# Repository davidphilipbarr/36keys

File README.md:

# So what we got here then? 

Behold. Here are some really basic PCBs that only support kailh choc low profile switches.

Currently they mostly have 36 keys (or less) which I consider to be as small as a keyboard can be without resorting to chording or other shenanigans.

Proceed with caution, and a little apprehension.

## About

The splits are heavily influenced by the following keyboards, and actually based on foostan's corne-light pin layout and pcb. 

* 5plit
* Gergoplex
* crkbd
* Kyria
* Jian/Jorne/Jorian
* Ferris
* Squiggle

## Caseless

These are all supposed to be used caseless and have no holes for cases or anything fancy.

## Firmware

Most 36 key split pcbs can use the crkbd firmware, but not the ones with no diodes, these all use the cradio firmware, maybe such things can be found [here](qmk). 
There is also a stripped back 36 key firmware called cranorm, which can be used instead of the crkbd firmware.

## FAQs

Aren't all the splits basically the same board with the keys shuffled around? Yes.

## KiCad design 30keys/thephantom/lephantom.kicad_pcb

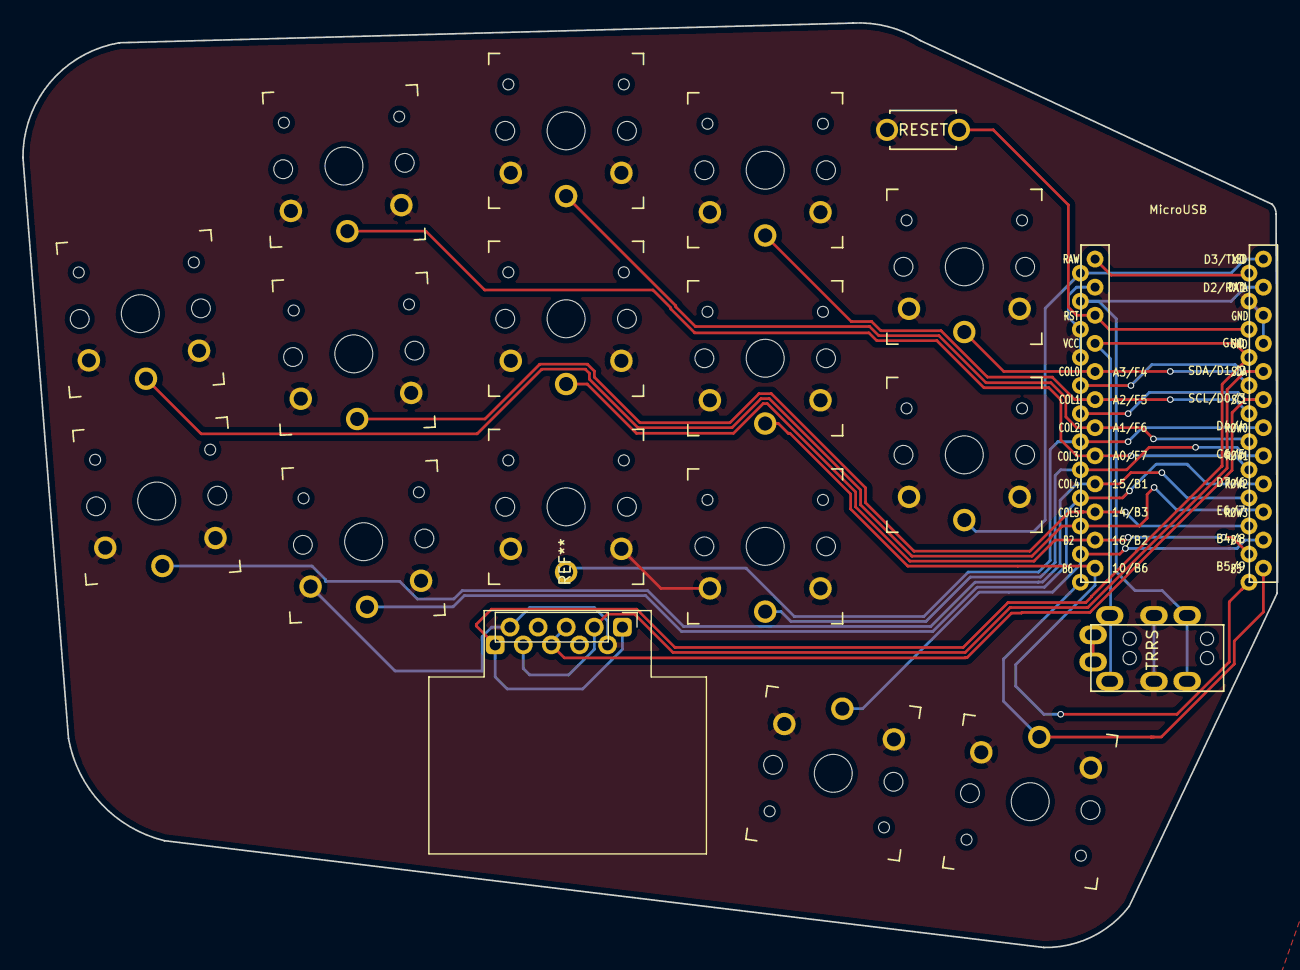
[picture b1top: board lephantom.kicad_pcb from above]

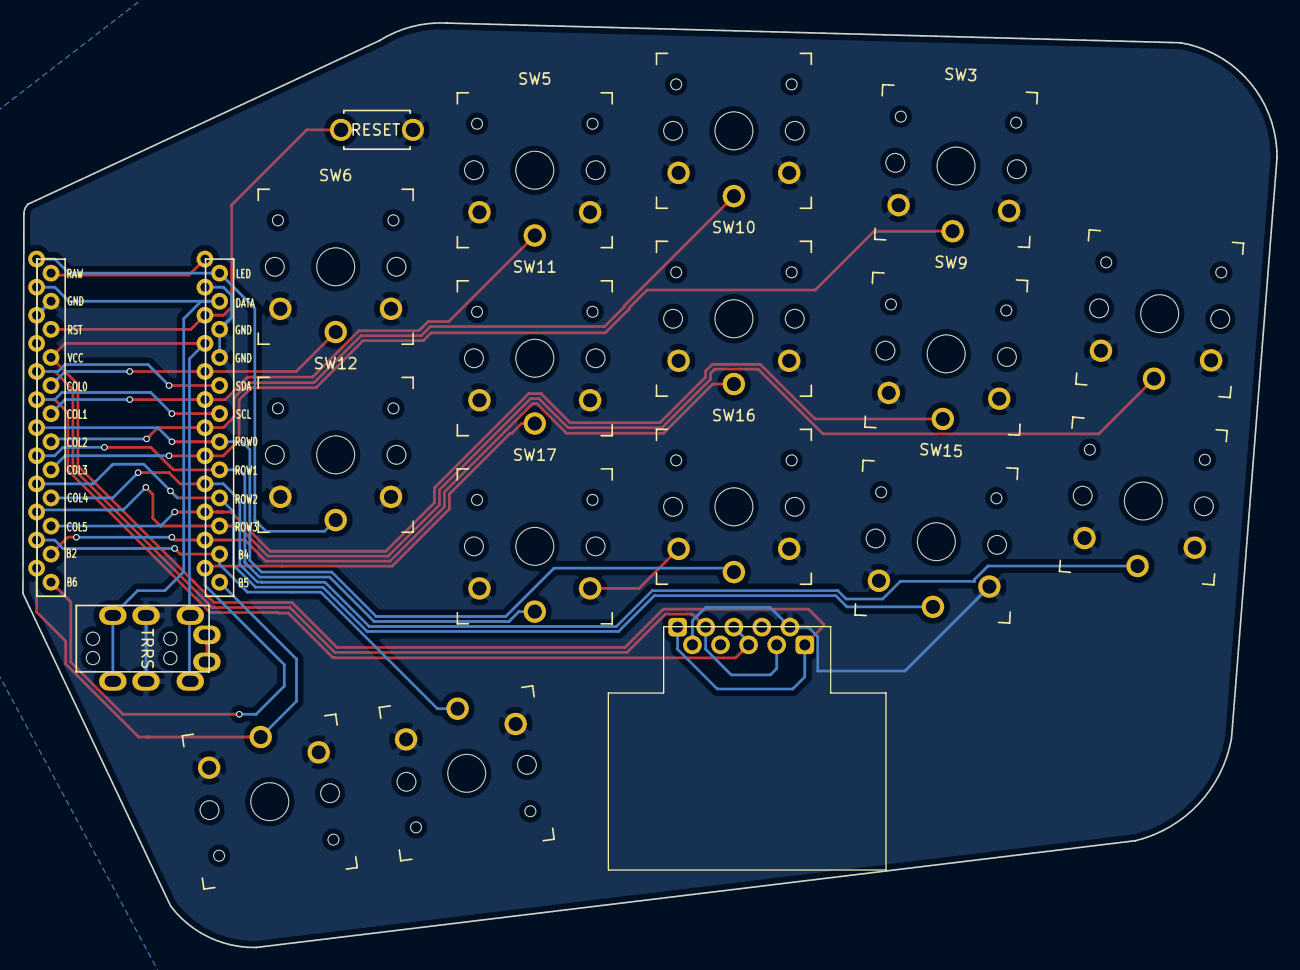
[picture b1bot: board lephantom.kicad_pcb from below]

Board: 2 copper layers, 113.4 x 83.6 mm, 18 parts (2 on the bottom side), 19 nets.

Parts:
J1: MJ-4PP-9
RSW1: Val**; ResetSW
SW2, SW3, SW4, SW5, SW6, SW8, SW9, SW10, SW11, SW12, SW15, SW16, SW17, SW20, SW21: SW_PUSH; SW_PG1350_reversible_b2
U1: ProMicro; ProMicro_v2

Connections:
GND: J1.C, RSW1.2, SW2.2, SW3.2, SW4.2, SW5.2, SW6.2, SW8.2, SW9.2, SW10.2, SW11.2, SW12.2, SW15.2, SW16.2, SW17.2, SW20.2, SW21.2, U1.3, U1.4, U1.23
LED: SW12.1, U1.1
unnamed: SW6.1, U1.20
unnamed: SW20.1, U1.11
unnamed: SW21.1, U1.12
unnamed: SW11.1, U1.13
unnamed: SW10.1, U1.14
VCC: J1.D, U1.21
col1: SW5.1, U1.19
col2: SW4.1, U1.18
col3: SW3.1, U1.17
col4: SW8.1, U1.16
col5: SW9.1, U1.15
data: J1.B, U1.2
reset: RSW1.1, U1.22
row0: SW16.1, U1.7
row1: SW17.1, U1.8
row2: SW15.1, U1.9
row3: SW2.1, U1.10

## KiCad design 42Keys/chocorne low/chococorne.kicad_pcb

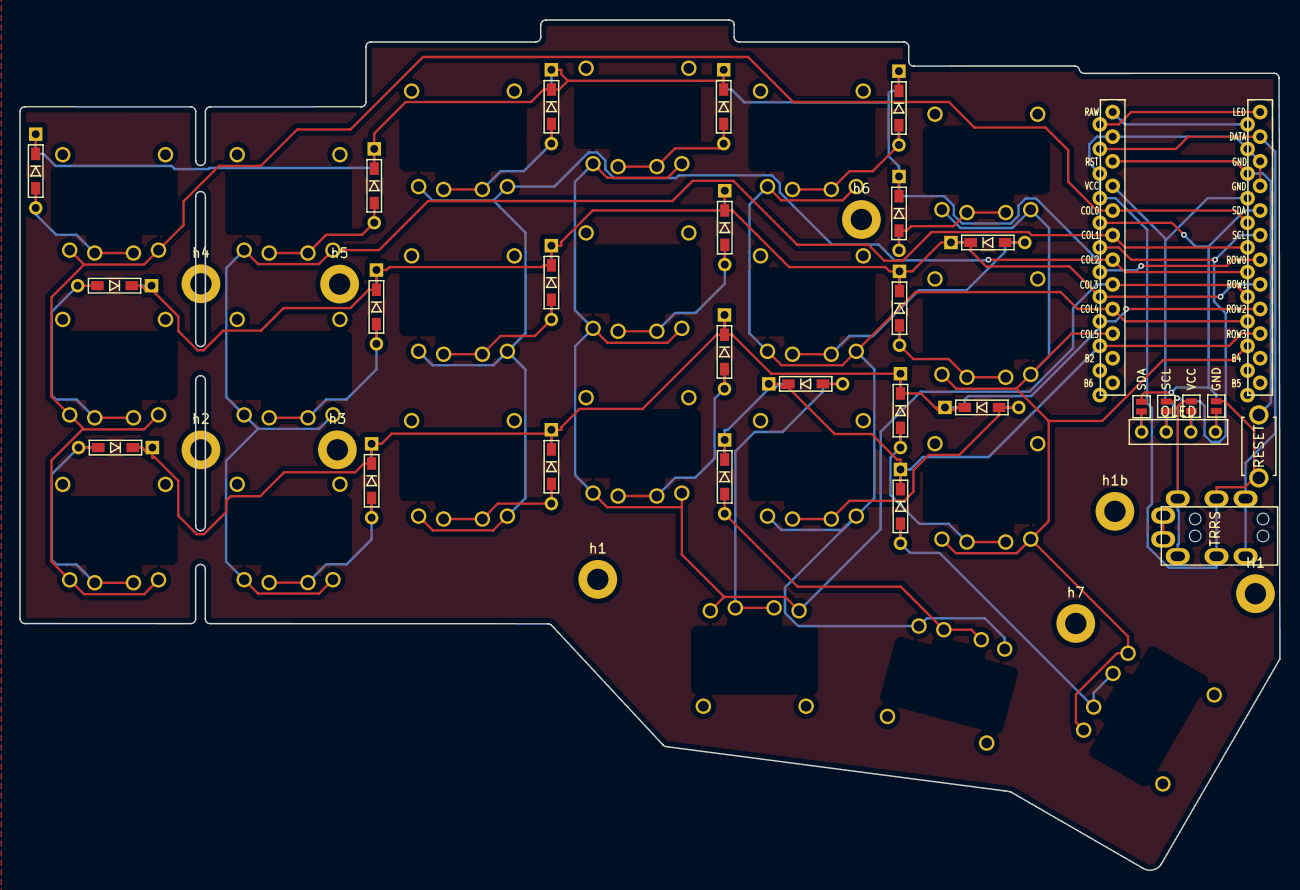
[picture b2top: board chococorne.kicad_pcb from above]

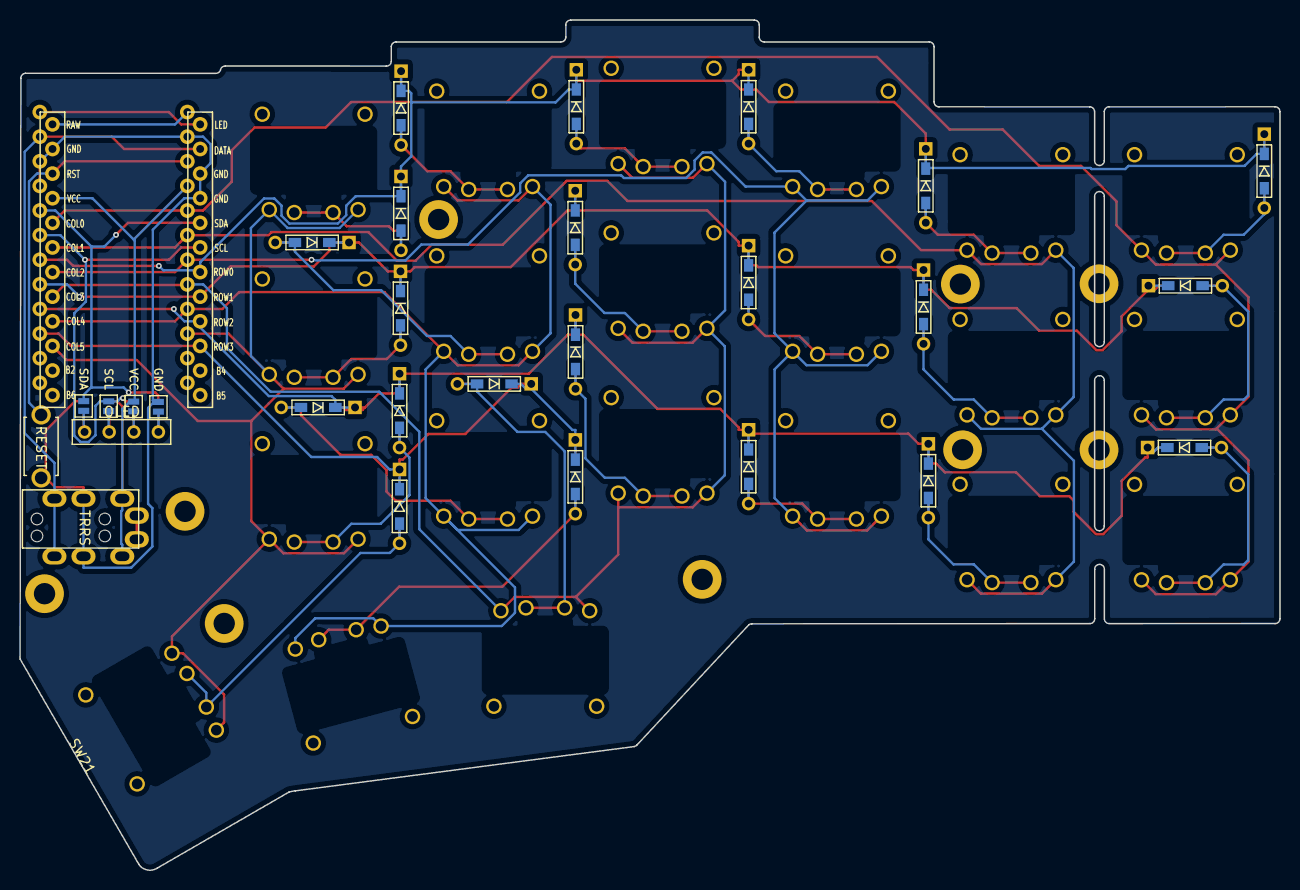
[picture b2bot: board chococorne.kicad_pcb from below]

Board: 2 copper layers, 130.0 x 87.7 mm, 63 parts (4 on the bottom side), 41 nets.

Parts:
D1, D2, D3, D4, D5, D6, D7, D8, D9, D10, D11, D12, D13, D14, D15, D16, D17, D18, D19, D20, D21: D; D3_TH_SMD
H1: h1; LEGO_HOLE
J1: MJ-4PP-9
J2: OLED
JP6, JP61: SDA; Jumper
JP62, JP68: GND; Jumper
JP63, JP66: SCL; Jumper
JP64, JP65: VCC; Jumper
RSW1: Val**; ResetSW
SW1, SW2, SW3, SW4, SW5, SW6, SW7, SW8, SW9, SW10, SW11, SW12, SW13, SW14, SW15, SW16, SW17, SW18, SW19, SW20, SW21: SW_PUSH; Kailh_PG1232
U1: ProMicro; ProMicro_v2
h1, h1b, h2, h3, h4, h5, h6, h7: h2; LEGO_HOLE

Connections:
GND: J1.C, JP62.1, JP68.1, RSW1.1, U1.3, U1.4, U1.23
unnamed: D1.2, SW1.2
unnamed: D2.2, SW2.2
unnamed: D3.2, SW3.2
unnamed: D4.2, SW4.2
unnamed: D5.2, SW5.2
unnamed: D6.2, SW6.2
unnamed: D7.2, SW7.2
unnamed: D8.2, SW8.2
unnamed: D9.2, SW9.2
unnamed: D10.2, SW10.2
unnamed: D11.2, SW11.2
unnamed: D12.2, SW12.2
unnamed: D13.2, SW13.2
unnamed: D14.2, SW14.2
unnamed: D15.2, SW15.2
unnamed: D16.2, SW16.2
unnamed: D17.2, SW17.2
unnamed: D18.2, SW18.2
unnamed: D19.2, SW19.2
unnamed: D20.2, SW20.2
unnamed: D21.2, SW21.2
unnamed: J2.3, JP65.2, JP66.2
unnamed: J2.4, JP6.2, JP68.2
unnamed: J2.2, JP63.2, JP64.2
unnamed: J2.1, JP61.2, JP62.2
SCL: JP63.1, JP66.1, U1.6
SDA: JP6.1, JP61.1, U1.5
VCC: J1.D, JP64.1, JP65.1, U1.21
col0: SW1.1, SW7.1, SW13.1, U1.20
col1: SW2.1, SW8.1, SW14.1, U1.19
col2: SW3.1, SW9.1, SW15.1, U1.18
col3: SW4.1, SW10.1, SW16.1, SW19.1, U1.17
col4: SW5.1, SW11.1, SW17.1, SW20.1, U1.16
col5: SW6.1, SW12.1, SW18.1, SW21.1, U1.15
data: J1.B, U1.2
reset: RSW1.2, U1.22
row0: D1.1, D2.1, D3.1, D4.1, D5.1, D6.1, U1.7
row1: D7.1, D8.1, D9.1, D10.1, D11.1, D12.1, U1.8
row2: D13.1, D14.1, D15.1, D16.1, D17.1, D18.1, U1.9
row3: D19.1, D20.1, D21.1, U1.10

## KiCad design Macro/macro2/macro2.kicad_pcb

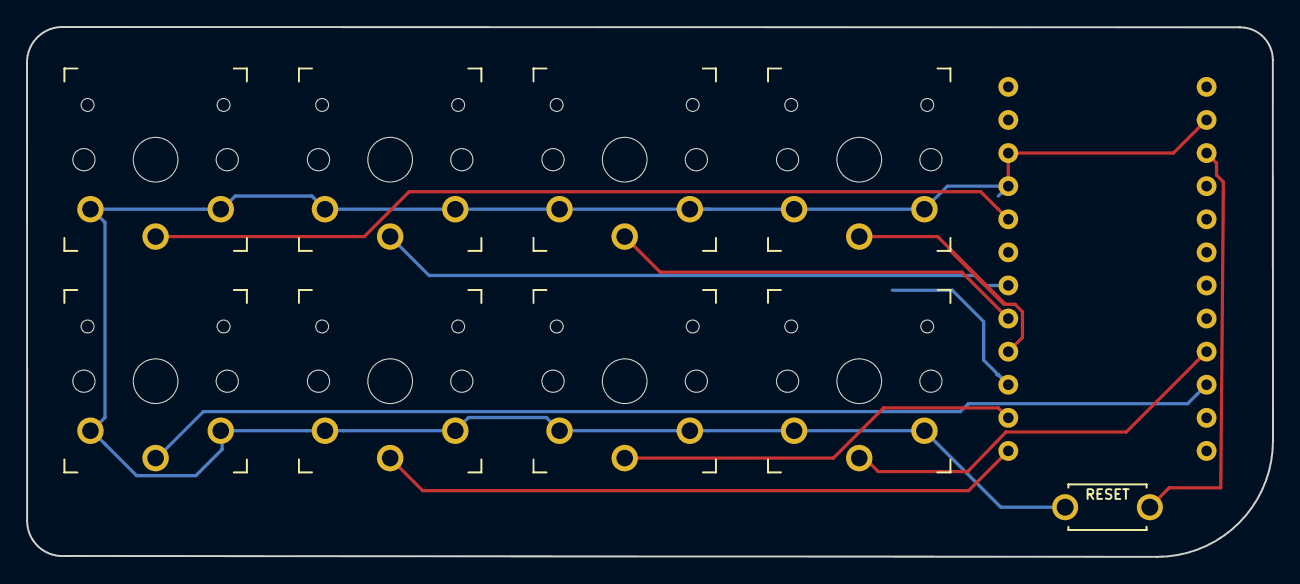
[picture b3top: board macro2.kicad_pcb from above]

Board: 2 copper layers, 95.6 x 40.7 mm, 10 parts (1 on the bottom side), 10 nets.

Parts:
RSW1: SW_Push; ResetSW_1side
SW1, SW2, SW3, SW4, SW5, SW6, SW7, SW8: SW_PUSH; SW_PG1350_reversible
U1: ProMicro_r; ProMicro_v3

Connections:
/RESET: RSW1.1, U1.22
/SW_1: SW1.1, U1.7
/SW_2: SW3.1, U1.8
/SW_3: SW4.1, U1.9
/SW_5: SW5.1, U1.11
/SW_6: SW6.1, U1.12
GND: RSW1.2, SW1.2, SW2.2, SW3.2, SW4.2, SW5.2, SW6.2, SW7.2, SW8.2, U1.3, U1.4, U1.23
unnamed: SW7.1, U1.5
unnamed: SW8.1, U1.15
unnamed: SW2.1, U1.16

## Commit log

2020-04-08 dump
2020-04-08 Cheap 36 keys 10x10
2020-04-08 36 keys ortho
2020-04-08 add snap
2020-04-08 Upload pictures
2020-04-08 Add pic, fix route.
2020-04-09 Add Simple README
2020-04-09 old pic
2020-04-09 update outline
2020-04-09 first of many spelling issues.
2020-04-09 edit spells
2020-04-09 add snaps
2020-04-09 formatting speeling
2020-04-11 Anglo
2020-04-13 corrections build stuff.
2020-04-13 additional corrections...
2020-04-23 Update, add gerber
2020-04-23 Updates, add edge cut, add gerber
2020-04-23 add crappy macro pad with encoder, might not even work.
2020-04-23 More recent image
2020-04-23 newer image
2020-04-23 Image
2020-04-23 Add more recent render
2020-05-01 fix last diode round corners
2020-05-01 no need
2020-05-01 out of date
2020-05-01 update gerber with fixes
2020-05-01 Add beak with deeper thumbs and more rounds
2020-05-01 fix promicro footprint
2020-05-01 add gerber, actually works...
2020-05-01 gerber things
2020-05-04 add no diodes
2020-05-13 Maybe don't wire q to raw?
2020-05-13 add a shit asetniop board, a nicer beak and a macropad with 6 buttons and 2 encoders
2020-05-13 image of working board
2020-05-14 rename files rotate thumbs
2020-05-14 imge
2020-06-01 Add ortho with drop pinky row.
2020-06-01 Crab 34 keys, no diodes
2020-06-02 Add crabby oblong crab thing
2020-06-03 some more accurate updates
2020-06-03 Add qmk for diodeless (sort of tested) and macro3
2020-06-03 add new bits
2020-06-03 link to things
2020-06-09 Add minimal qmk instead of using crkbd (still works with crkbd firmware)
2020-06-09 Add mini axe type layout.
2020-06-11 oops
2020-06-11 update keymaps
2020-06-21 pikture
2020-07-04 Macro 1?
2020-07-04 pasty pad
2020-07-10 Update to make more sense
2020-07-10 all the encoders
2020-07-15 pg1232 switches
2020-07-17 half baked
2020-07-17 disaster
2020-07-18 ginnybased hex
2020-07-21 Add ferris kyria type board thing
2020-07-21 Add pic
2020-07-27 big tidy
2020-07-28 Better tidy up, remove duplicates, doh.
2020-07-28 better tidy, remove duplicates, add images and little bit of info
2020-07-28 remove last dup
2020-07-28 formatting
2020-07-28 add back s
2020-07-28 Add back besom s
2020-07-28 More info
2020-08-07 Add some absolem to cradio
2020-08-07 Cradio with soft curve and slight tweak to thumbs
2020-08-10 fix promicro footprint, centre ferris move thumbs.
2020-08-10 let's get these thumbs something like ferris
2020-08-16 add basic bluemicro firmware
2020-09-01 curve changes
2020-09-03 36 key no diodes for use with bluetooth boards .
2020-09-03 no trrs
2020-09-03 add sweep with shape from ferris compact
2020-09-06 add dubious on off switch
2020-09-08 add pg1232 cradio
2020-09-08 the last one was so bad, it required a sequel
2020-09-08 add cradio itself
2020-09-08 32 key gang
2020-09-26 not 36 keys
2020-09-26 But, is it a corne?
2020-09-28 Add back break off, 'fix' 1.5u footprint (maybe) move bits around.
2020-09-28 tweaks
2020-10-02 more
2020-10-14 add gerberer
2020-10-15 update keymap biz
2020-10-16 fix screens?
2020-10-17 really fix screen, try not to route vcc to gnd...
2020-10-17 manual routing.
2020-10-17 manual routing for ferris sweep.
2020-10-17 fixed some wilding tracks.
2020-10-20 holes for theoretical corne case?
2020-11-09 missing link
2020-11-14 add pg1232 corne
2020-11-24 Lots of changes
2020-11-27 move macro pads
2021-01-08 Add files via upload
    Add stl and modified pcb from Tom Barnes. add initial readme.
2021-01-19 add phantom 30key
2021-02-26 this is really haiha 2
2021-08-03 slightly improved routing, still total trainwreck.
